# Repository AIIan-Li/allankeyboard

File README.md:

# Allan's keyboard
### About:
A 75% keyboard with a custom case. All parts under $150 USD, uses screw in stabilisers, and has akko v3 yellow switches along with M3 heatset inserts and screws. I made this project to learn more about CAD and making hardware projects. I thought it would be a reasonable next step after a macropad (was way harder actually) however I got to challenge myself and learn new things. 

[project demo](https://youtu.be/CJazeotiTts)
[good project demo](https://youtu.be/POquT2XbD1o)
### Case:

The case was made in Fusion 360 and is gasket mounted. 8 screws to ensure the keyboard is secure when printing in two parts. 

### Firmware:

The firmware was made with KMK however I intend to recreate firmware in ZMK for full bluetooth capabilities( I am currently learning as I don't want to just copilot/vibecode everything)

### Images:

Schematic

PCB

Case

### BOM:
| Item                          | Cost (USD)   | Cost (CAD)   | Link                                                                                                                                                                         |
| ----------------------------- | ------------ | ------------ | ---------------------------------------------------------------------------------------------------------------------------------------------------------------------------- |
| Akko V3 Cream Yellow Switches | \$33.00      | \$45.00      | [https://www.amazon.ca/Akko-Keyboard-Dustproof-Mechanical-Switches/dp/B0C3H8NVJV/](https://www.amazon.ca/Akko-Keyboard-Dustproof-Mechanical-Switches/dp/B0C3H8NVJV/)         |
| 3D Printer Filament (PLA 1kg) | \$21.00      | \$28.00      | [https://www.amazon.ca/ELEGOO-Filament-Dimensional-Accuracy-Compatible/dp/B0BM4F65SL/](https://www.amazon.ca/ELEGOO-Filament-Dimensional-Accuracy-Compatible/dp/B0BM4F65SL/) |
| PCB x5 (min quantity)         | \$0.00       | \$0.00       | [https://jlcpcb.com](https://jlcpcb.com)                                                                                                                                     |
| 1N4148 Diodes x100            | \$1.50       | \$2.00       | [https://www.aliexpress.com/item/1005003194692663.html](https://www.aliexpress.com/item/1005003194692663.html)                                                               |
| Durock V3 Stabilizers         | \$10.00      | \$13.00      | [https://www.aliexpress.com/item/1005002192386317.html](https://www.aliexpress.com/item/1005002192386317.html)                                                               |
| Heatset Inserts               | \$5.10       | \$7.00       | [https://www.aliexpress.com/item/1005006472962973.html](https://www.aliexpress.com/item/1005006472962973.html)                                                               |
| nice!nano v2                  | \$44.00      | \$60.00      | [https://typeractive.xyz/products/nice-nano](https://typeractive.xyz/products/nice-nano)                                                                                     |
| Keycaps                       | \$9.00       | \$12.00      | [https://www.aliexpress.com/item/1005007321700850.html](https://www.aliexpress.com/item/1005007321700850.html)                                                               |
| Screws                        | \$1.80       | \$2.50       | [https://www.aliexpress.com/item/4000056753202.html](https://www.aliexpress.com/item/4000056753202.html)                                                                     |
|                               |              |              |                                                                                                                                                                               |

| **Total (Shipping included)** | **\$123.60** | **\$170.00** |                                                                                                                                                                              |

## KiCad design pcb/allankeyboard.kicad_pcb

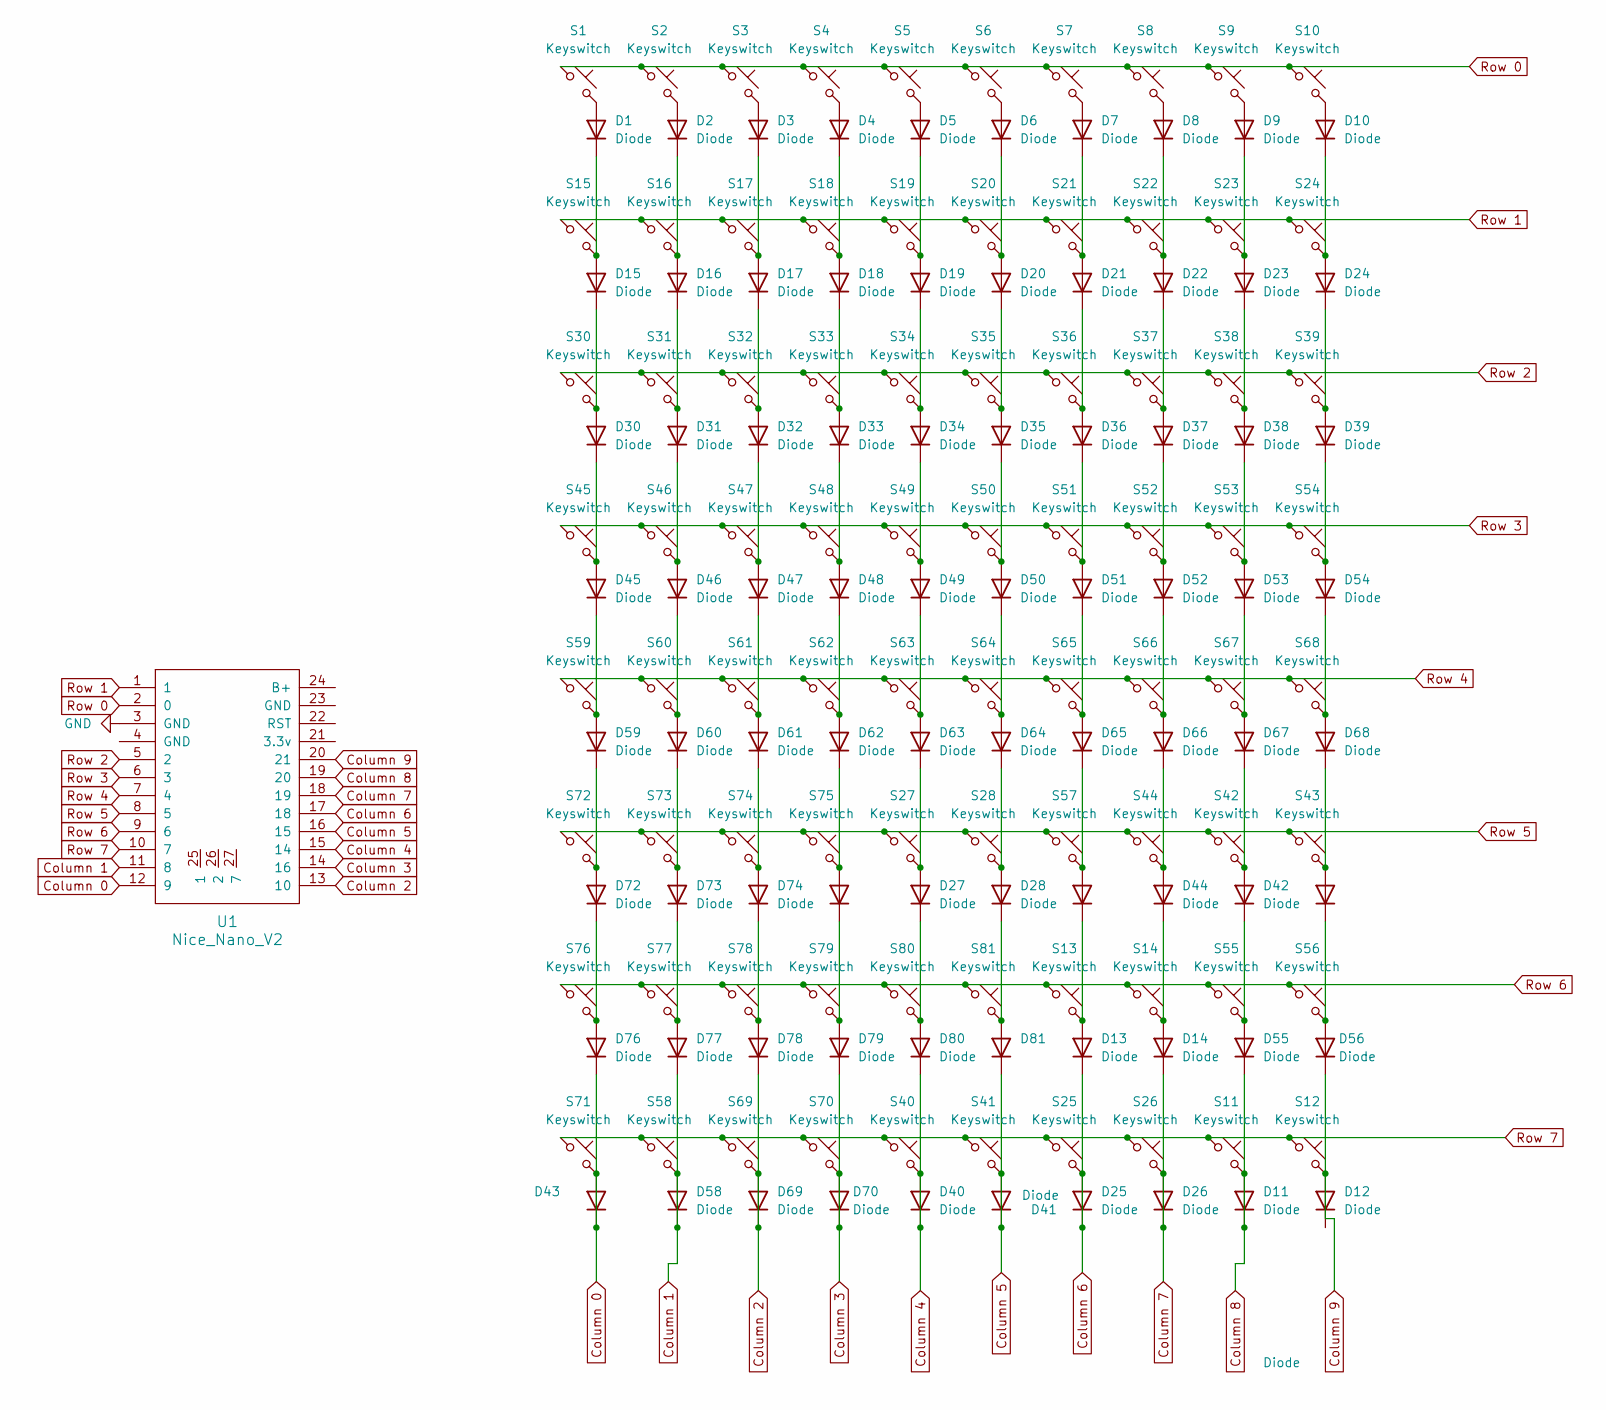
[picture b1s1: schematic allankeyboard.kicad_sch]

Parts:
D1, D2, D3, D4, D5, D6, D7, D8, D9, D10, D11, D12, D13, D14, D15, D16, D17, D18, D19, D20, D21, D22, D23, D24, D25, D26, D27, D28, D30, D31, D32, D33, D34, D35, D36, D37, D38, D39, D40, D41, D42, D43, D44, D45, D46, D47, D48, D49, D50, D51, D52, D53, D54, D55, D56, D57, D58, D59, D60, D61, D62, D63, D64, D65, D66, D67, D68, D69, D70, D71, D72, D73, D74, D75, D76, D77, D78, D79, D80, D81: Diode; D_DO-35_SOD27_P7.62mm_Horizontal
S1, S2, S3, S4, S5, S6, S7, S8, S9, S10, S11, S12, S13, S14, S15, S16, S17, S18, S19, S20, S21, S22, S23, S24, S25, S26, S27, S31, S32, S33, S34, S35, S36, S37, S38, S39, S40, S41, S42, S44, S46, S47, S48, S49, S50, S51, S52, S53, S54, S55, S56, S58, S60, S61, S62, S63, S64, S65, S66, S67, S68, S69, S71, S76, S77, S78, S79, S80, S81: Keyswitch; SW_Cherry_MX_1.00u_PCB
S28: Keyswitch; SW_Cherry_MX_2.00u_PCB
S30: Keyswitch; SW_Cherry_MX_1.50u_Plate
S43: Keyswitch; SW_Cherry_MX_1.50u_PCB
S45, S70: Keyswitch; SW_Cherry_MX_1.75u_PCB
S57, S59: Keyswitch; SW_Cherry_MX_2.25u_PCB
S72, S73, S74: Keyswitch; SW_Cherry_MX_1.25u_PCB
S75: Keyswitch; SW_Cherry_MX_6.25u_PCB
U1: Nice_Nano_V2

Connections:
Column 0: D71.1 (K), D71.2 (A), D76.1 (K), S71.2, U1.12 (9)
Column 1: D58.1 (K), D58.2 (A), D77.1 (K), S58.2, U1.11 (8)
Column 2: D69.1 (K), D69.2 (A), D78.1 (K), S69.2, U1.13 (10)
Column 3: D70.1 (K), D70.2 (A), D79.1 (K), S70.2, U1.14 (16)
Column 4: D40.1 (K), D40.2 (A), D80.1 (K), S40.2, U1.15 (14)
Column 5: D41.1 (K), D41.2 (A), D81.1 (K), S41.2, U1.16 (15)
Column 6: D13.1 (K), D25.1 (K), D25.2 (A), S25.2, U1.17 (18)
Column 7: D14.1 (K), D26.1 (K), D26.2 (A), S26.2, U1.18 (19)
Column 8: D11.1 (K), D11.2 (A), D55.1 (K), S11.2, U1.19 (20)
Column 9: D12.2 (A), D56.1 (K), S12.2, U1.20 (21)
GND: U1.3 (GND)
unnamed: D1.2 (A), S1.2
unnamed: D1.1 (K), D15.2 (A), S15.2
unnamed: D2.2 (A), S2.2
unnamed: D3.2 (A), S3.2
unnamed: D4.2 (A), S4.2
unnamed: D5.2 (A), S5.2
unnamed: D6.2 (A), S6.2
unnamed: D7.2 (A), S7.2
unnamed: D8.2 (A), S8.2
unnamed: D9.2 (A), S9.2
unnamed: D10.2 (A), S10.2
unnamed: D10.1 (K), D24.2 (A), S24.2
unnamed: D13.2 (A), D57.1 (K), S13.2
unnamed: D14.2 (A), D44.1 (K), S14.2
unnamed: D15.1 (K), D30.2 (A), S30.2
unnamed: D2.1 (K), D16.2 (A), S16.2
unnamed: D16.1 (K), D31.2 (A), S31.2
unnamed: D3.1 (K), D17.2 (A), S17.2
unnamed: D17.1 (K), D32.2 (A), S32.2
unnamed: D4.1 (K), D18.2 (A), S18.2
unnamed: D18.1 (K), D33.2 (A), S33.2
unnamed: D5.1 (K), D19.2 (A), S19.2
unnamed: D19.1 (K), D34.2 (A), S34.2
unnamed: D6.1 (K), D20.2 (A), S20.2
unnamed: D20.1 (K), D35.2 (A), S35.2
unnamed: D7.1 (K), D21.2 (A), S21.2
unnamed: D21.1 (K), D36.2 (A), S36.2
unnamed: D8.1 (K), D22.2 (A), S22.2
unnamed: D22.1 (K), D37.2 (A), S37.2
unnamed: D9.1 (K), D23.2 (A), S23.2
unnamed: D23.1 (K), D38.2 (A), S38.2
unnamed: D24.1 (K), D39.2 (A), S39.2
unnamed: D27.2 (A), D63.1 (K), S27.2
unnamed: D27.1 (K), D80.2 (A), S80.2
unnamed: D28.2 (A), D64.1 (K), S28.2
unnamed: D28.1 (K), D81.2 (A), S81.2
unnamed: D30.1 (K), D45.2 (A), S45.2
unnamed: D31.1 (K), D46.2 (A), S46.2
unnamed: D32.1 (K), D47.2 (A), S47.2
unnamed: D33.1 (K), D48.2 (A), S48.2
unnamed: D34.1 (K), D49.2 (A), S49.2
unnamed: D35.1 (K), D50.2 (A), S50.2
unnamed: D36.1 (K), D51.2 (A), S51.2
unnamed: D37.1 (K), D52.2 (A), S52.2
unnamed: D38.1 (K), D53.2 (A), S53.2
unnamed: D39.1 (K), D54.2 (A), S54.2
unnamed: D42.2 (A), D67.1 (K), S42.2
unnamed: D42.1 (K), D55.2 (A), S55.2
unnamed: D43.2 (A), D68.1 (K), S43.2
unnamed: D43.1 (K), D56.2 (A), S56.2
unnamed: D44.2 (A), D66.1 (K), S44.2
unnamed: D45.1 (K), D59.2 (A), S59.2
unnamed: D46.1 (K), D60.2 (A), S60.2
unnamed: D47.1 (K), D61.2 (A), S61.2
unnamed: D48.1 (K), D62.2 (A), S62.2
unnamed: D49.1 (K), D63.2 (A), S63.2
unnamed: D50.1 (K), D64.2 (A), S64.2
unnamed: D51.1 (K), D65.2 (A), S65.2
unnamed: D52.1 (K), D66.2 (A), S66.2
unnamed: D53.1 (K), D67.2 (A), S67.2
unnamed: D54.1 (K), D68.2 (A), S68.2
unnamed: D57.2 (A), D65.1 (K), S57.2
unnamed: D59.1 (K), D72.2 (A), S72.2
unnamed: D60.1 (K), D73.2 (A), S73.2
unnamed: D61.1 (K), D74.2 (A), S74.2
unnamed: D62.1 (K), D75.2 (A), S75.2
unnamed: D72.1 (K), D76.2 (A), S76.2
unnamed: D73.1 (K), D77.2 (A), S77.2
unnamed: D74.1 (K), D78.2 (A), S78.2
unnamed: D75.1 (K), D79.2 (A), S79.2
Row 0: S1.1, S2.1, S3.1, S4.1, S5.1, S6.1, S7.1, S8.1, S9.1, S10.1, U1.2 (0)
Row 1: S15.1, S16.1, S17.1, S18.1, S19.1, S20.1, S21.1, S22.1, S23.1, S24.1, U1.1
Row 2: S30.1, S31.1, S32.1, S33.1, S34.1, S35.1, S36.1, S37.1, S38.1, S39.1, U1.5 (2)
Row 3: S45.1, S46.1, S47.1, S48.1, S49.1, S50.1, S51.1, S52.1, S53.1, S54.1, U1.6 (3)
Row 4: S59.1, S60.1, S61.1, S62.1, S63.1, S64.1, S65.1, S66.1, S67.1, S68.1, U1.7 (4)
Row 5: S27.1, S28.1, S42.1, S43.1, S44.1, S57.1, S72.1, S73.1, S74.1, S75.1, U1.8 (5)
Row 6: S13.1, S14.1, S55.1, S56.1, S76.1, S77.1, S78.1, S79.1, S80.1, S81.1, U1.9 (6)
Row 7: S11.1, S12.1, S25.1, S26.1, S40.1, S41.1, S58.1, S69.1, S70.1, S71.1, U1.10 (7)

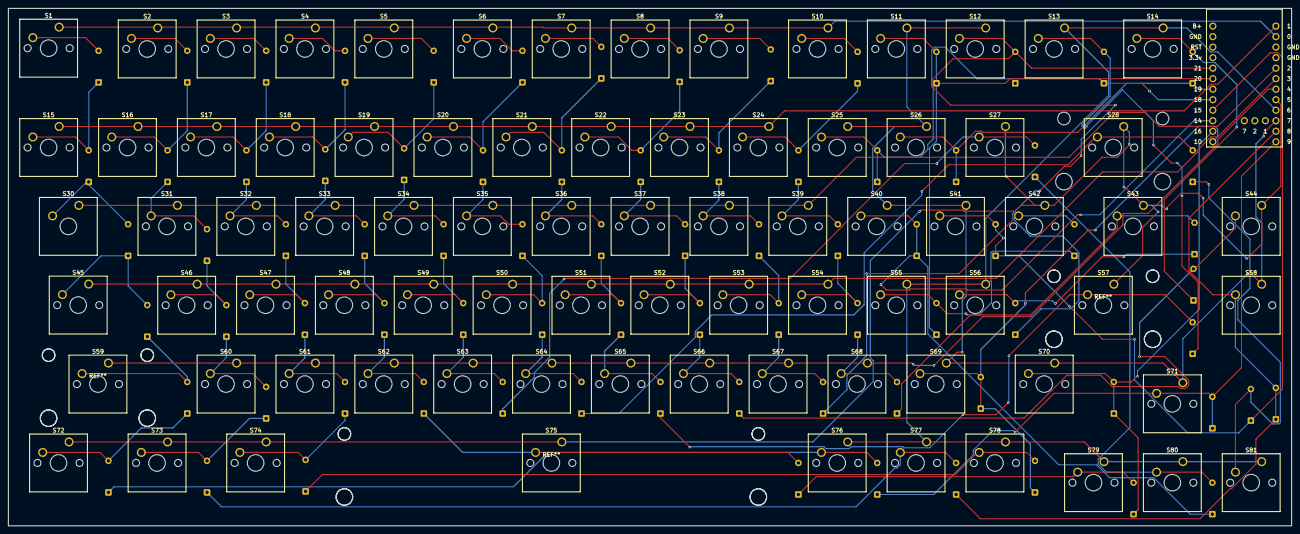
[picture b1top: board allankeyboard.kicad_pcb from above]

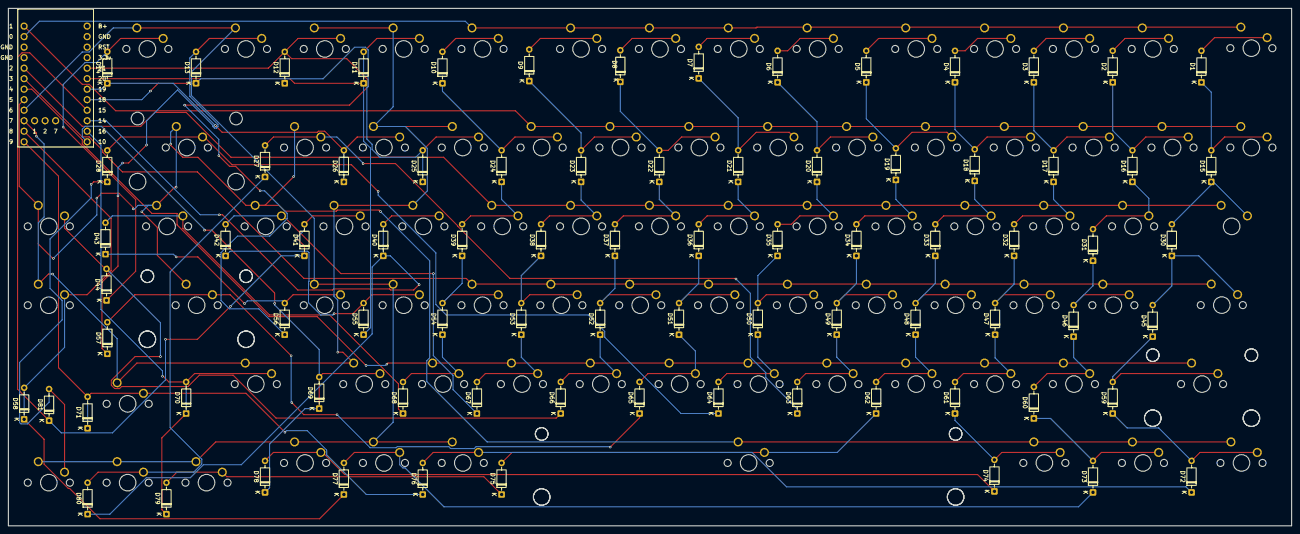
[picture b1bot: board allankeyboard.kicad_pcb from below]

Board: 2 copper layers, 310.0 x 125.0 mm, 161 parts (81 on the bottom side), 88 nets.

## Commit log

2025-06-13 updated journal.md
2025-06-24 added journal.md and pcb files
2025-06-24 Finished Jounraling, added all step files and complete BOM
2025-06-24 fix BOM formating
2025-06-24 fix bom (again)
2025-06-26 added links to BOM
2025-06-26 empty
2025-06-26 added bom
2025-08-02 completed journal updated everything
2025-08-02 finished readme
2025-08-02 finish readme
